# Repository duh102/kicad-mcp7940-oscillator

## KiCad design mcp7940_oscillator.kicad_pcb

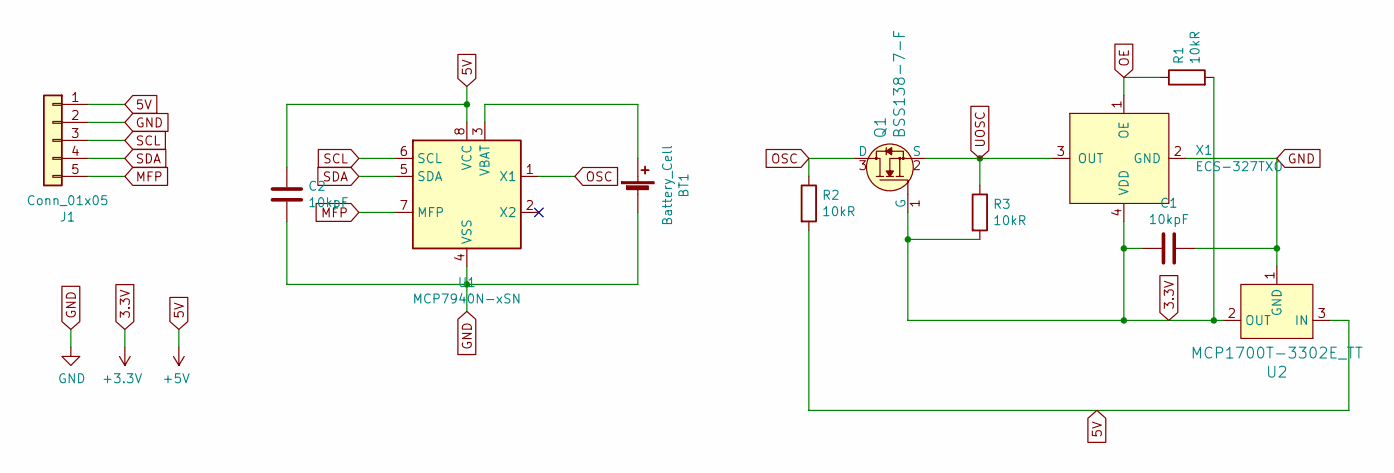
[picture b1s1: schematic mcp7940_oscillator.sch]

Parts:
BT1: Battery_Cell; BatteryHolder_Keystone_2894_CR1220
C1, C2: 10kpF; C_0603_1608Metric
J1: Conn_01x05; PinHeader_1x05_P2.54mm_Vertical
Q1: BSS138-7-F; SOT-23-3; MPN BSS138-7-F; Digi-Key_PN BSS138-FDICT-ND
R1, R2, R3: 10kR; R_0805_2012Metric
U1: MCP7940N-xSN; SOIC-8_3.9x4.9mm_P1.27mm
U2: MCP1700T-3302E_TT; SOT-23-3; MPN MCP1700T-3302E/TT; Digi-Key_PN MCP1700T3302ETTCT-ND
X1: ECS-327TXO; ECS-327MVATX-3

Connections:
3.3V: C1.2, Q1.1 (G), R1.2, R3.2, U2.2 (OUT), X1.4 (VDD)
5V: C2.1, J1.1, R2.2, U1.8 (VCC), U2.3 (IN)
GND: BT1.2 (-), C1.1, C2.2, J1.2, U1.4 (VSS), U2.1 (GND), X1.2 (GND)
MFP: J1.5, U1.7 (MFP)
unnamed: BT1.1 (+), U1.3 (VBAT)
OE: R1.1, X1.1 (OE)
OSC: Q1.3 (D), R2.1, U1.1 (X1)
SCL: J1.3, U1.6 (SCL)
SDA: J1.4, U1.5 (SDA)
UOSC: Q1.2 (S), R3.1, X1.3 (OUT)

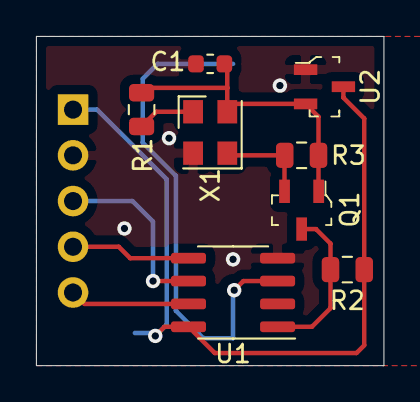
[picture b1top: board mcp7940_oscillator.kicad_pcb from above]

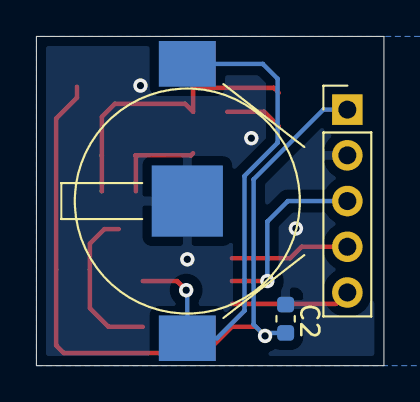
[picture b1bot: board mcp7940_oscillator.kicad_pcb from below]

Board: 2 copper layers, 19.3 x 18.3 mm, 11 parts (3 on the bottom side), 10 nets.

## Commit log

2020-12-09 Rescue
